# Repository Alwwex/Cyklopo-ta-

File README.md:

# CykloComp – chytrý cyklopočítač (ESP32-C3) + aplikace + PCB + krabička

Vlastní „Garmin“ na řídítka: **Waveshare ESP32-C3-Zero**, barevný displej
ST7789, GPS a Li-Po baterie. Zobrazuje rychlost, trasu s mapou ulic, tep a
kadenci z BLE senzorů, ukládá jízdy a přes Bluetooth si povídá s aplikací
v telefonu. Vzhled je inspirovaný „DS / Game Boy“ cyklopočítači – barevný
budík rychlosti a retro zelené LCD téma.

| Plošný spoj CykloPCB v1 | 3D krabička s Garmin úchytem |
|---|---|
|  |  |

## Co je v repozitáři

| Složka | Co to je |
|---|---|
| [`firmware/CykloComp/`](firmware/CykloComp/CykloComp.ino) | firmware v2 pro ESP32-C3 (Arduino IDE) |
| [`firmware/host_preview/`](firmware/host_preview/) | náhled displeje na PC – stejný kód vykreslí obrazovky do PNG (bez hardwaru) |
| [`webapp/`](webapp/README.md) | **mobilní aplikace** (PWA, Web Bluetooth) – doporučená |
| [`app/`](app/README.md) | původní React Native aplikace (kompatibilní, dál se nevyvíjí) |
| [`hardware/pcb/`](hardware/pcb/README.md) | plošný spoj ve 2 variantách: osazení u JLCPCB, nebo holá deska na ruční pájení |
| [`hardware/enclosure/`](hardware/enclosure/README.md) | 3D tištěná krabička (OpenSCAD + STL), Garmin quarter-turn |
| [`tools/usb_console.py`](tools/usb_console.py) | ladění přes USB bez telefonu |
| [`docs/NAKUP.md`](docs/NAKUP.md) | **co doobjednat** |
| [`docs/DOPORUCENI.md`](docs/DOPORUCENI.md) | web vs. nativní appka, lepší displej, lepší nabíjení |

## Rychlý start

1. **Firmware** – Arduino IDE, deska *ESP32C3 Dev Module*,
   *USB CDC On Boot: Enabled*, *Partition Scheme: Default 4MB with spiffs*.
   Knihovny: `Adafruit GFX`, `Adafruit ST7735 and ST7789`, `TinyGPSPlus`,
   `NimBLE-Arduino` **2.x**. V `CykloComp.ino` vyber `BOARD_PROFILE`
   (`BOARD_BREADBOARD` = současné zapojení, `BOARD_CYKLOPCB_V1` = nový plošný spoj)
   a nahraj. Bez GPS signálu to vyzkoušíš příkazem `SIM:1` (USB nebo appka).
2. **Aplikace** – otevři `webapp/` v Chrome na Androidu (návod na nasazení v
   [webapp/README.md](webapp/README.md)) → *Připojit CykloComp*. Bez hardwaru:
   *Vyzkoušet demo*.
3. **PCB** – buď JLC osadí malé součástky (`hardware/pcb/build/` – gerber zip
   + BOM + CPL), nebo objednáš **jen holou desku a všechno připájíš sám**
   (`hardware/pcb/build_rucni/`, velké součástky + tvůj modul TP4056)
   ([postup pro obě varianty](hardware/pcb/README.md)).
4. **Krabička** – změř displej a baterii, uprav parametry a vytiskni
   ([postup](hardware/enclosure/README.md)). Nejdřív `garmin_test.stl`!

## Firmware v2

### Ovládání

| Tlačítko | Krátce | Dlouze |
|---|---|---|
| **MODE** (BTN1) | další obrazovka | vypnout (spánek, probudí MODE – jen na PCB) |
| **START** (BTN2) | start / stop jízdy (po stopu souhrn jízdy) | vynulovat trip |
| **PAUZA** (BTN3) | při jízdě pauza/pokračovat, jinak předchozí obrazovka | přepnout téma NOC → RETRO → DEN |

První stisk při ztlumeném displeji jen rozsvítí.

### Obrazovky
1. **DASH** – barevný oblouk rychlosti (šipky = průměr a maximum), velké
   7-segmentové číslice, čas jízdy a 4 nastavitelné dlaždice (z 14 hodnot:
   trip, čas, průměr, max, výška, odometr, satelity, hodiny, stoupání, sklon,
   tep, kadence, baterie, do cíle).
2. **STATISTIKY** – kompletní přehled jízdy + odometr.
3. **MAPA** – trasa z appky, ulice z OpenStreetMap, projetá stopa, šipka směru,
   „DO CÍLE“ a rychloměrný proužek jako na Game Boyi.
4. **SYSTÉM** – GPS, poloha, HDOP, baterie, Bluetooth, senzory, verze.

### Co umí navíc proti v1
- 3 témata (**NOC** – tmavá DS deska, **RETRO** – Game Boy zelená, **DEN** – kontrast na slunce)
- **jízdy se ukládají do flash** (LittleFS, posledních 40) a appka si je stáhne → telefon nemusí být během jízdy připojený
- **autopauza**, **stoupání** (s hysterezí), **sklon**, filtrace skoků GPS a špatného HDOP
- **baterie** (%, nabíjení přes USB, varování, vypnutí při vybití), **jas podsvícení**, ztlumení při stání
- **spánek** a automatické vypnutí po nečinnosti (PCB), vypínání GPS
- **BLE senzory**: hrudní pás (Heart Rate 0x180D) a kadence (CSC 0x1816) – běží ve vlastním vlákně
- hodiny z telefonu, když GPS ještě nemá čas
- příkazy z BLE se zpracovávají ve smyčce (žádné souběhy s kreslením)
- **simulace jízdy** `SIM:1` – jede po nahrané trase, ukáže i autopauzu

Kód je jeden `.ino` (podmínka Arduino IDE – ve složce sketche jen jeden `.ino`).

### Náhled displeje na PC
`firmware/host_preview/build_preview.sh` přeloží **ten samý** `CykloComp.ino`
pro PC (displej = pole pixelů), odsimuluje jízdu a uloží PNG všech obrazovek ve
všech tématech – hodí se při úpravách vzhledu bez nahrávání do ESP.

## BLE protokol (firmware ↔ appka)

Service `a5c40001-2f0b-4f6e-9d3a-8c1e2b7d9f10`, charakteristiky `a5c4000X-…`:

| UUID | Typ | Obsah |
|---|---|---|
| `…0002` telemetrie | READ + NOTIFY, 1×/s | `{"fix","spd","lat","lng","alt","dst","tim","sat","rid","pau","bat","asc","max","hr","cad"}` (≤ 173 B) |
| `…0003` příkazy | WRITE + WRITE_NR | textové příkazy níže (≤ 255 B) |
| `…0004` stav | READ + NOTIFY, 1×/5 s | `{"fw","brd","odo","vb","chg","thm","bl","ap","sen","hrc","csc","grd","avg","hdp","crs","scr","tz","aoff","gmax","sim","apa","fs","rcur","f":[…]}` |
| `…0005` bulk | READ | odpovědi na `SYNC:*` (`{"req":"…",…}`, ≤ 512 B) |

`bat` = 0–100 %, 101 = napájení z USB, −1 = neměří se.

Příkazy:
- jízda: `RIDE:START|STOP|PAUSE|RESUME`, `RESET_TRIP`
- čas: `SET_TZ:<h>`, `TIME:<unix>`
- displej: `SCREEN:<0-3>`, `THEME:<0-2>`, `BL:<5-100>`, `GAUGE:<km/h>`, `CFG:FIELDS:a,b,c,d` (0–13)
- chování: `AP:0|1` (autopauza), `SENS:0|1` (BLE senzory), `AUTOOFF:<min>`, `ODO:<km>`, `SIM:0|1`, `PWROFF`, `INFO`
- trasa: `RT:BEGIN` / `RT:P:lat,lng;…` / `RT:END` / `RT:CLEAR`
- ulice: `MP:BEGIN` / `MP:P:…` / `MP:END` (segmenty oddělené `999,999`)
- uložené jízdy: `SYNC:LIST`, `SYNC:SUM:<id>`, `SYNC:TRK:<id>:<strana>` (24 bodů/strana), `SYNC:DEL:<id>` →
  odpověď se přečte z bulk charakteristiky (appka čte, dokud `req` neodpovídá dotazu)

Stará React Native appka funguje dál – nová pole ignoruje.

## Testování přes USB (bez telefonu)

Firmware zvládá **stejný textový protokol i po USB** (nativní USB-CDC).

1. Arduino IDE: **Tools → USB CDC On Boot → Enabled**.
2. Serial Monitor (115200) nebo `python3 tools/usb_console.py [PORT]` (`pip install pyserial`).
3. Piš příkazy (`SIM:1`, `RIDE:START`, `THEME:1`, `SYNC:LIST`…) a sleduj
   telemetrii (1×/s), `STATUS:` (1×/5 s) a odpovědi `BULK:`.
   `usb_console.py` umí `testroute` – pošle ukázkovou trasu.

## Akceptační test (ruční, na reálném HW)

1. **Připojení** – appka najde `CykloComp`, telemetrie teče do 2 s, hodiny na displeji se nastaví z telefonu.
2. **Start z appky** – oba ukazují 0:00, na displeji červená tečka.
3. **Pauza** – z appky → na ESP žluté `‖`, čas stojí; PAUZA na ESP → v appce zmizí badge.
4. **Autopauza** – při zastavení se čas po 3 s zastaví („AUTOPAUZA“).
5. **Start/stop z ESP** a **jízda bez telefonu** – po STOP souhrn jízdy; po připojení appky se jízda stáhne do Historie (s mapou a body).
6. **Trasa** – naplánovat v Mapě (nebo GPX) → *Odeslat* → na displeji trasa + ulice + „DO CÍLE“.
7. **Rychlost při stání** – `0.0`, ne GPS šum.
8. **Nastavení** – téma, jas, dlaždice 2×2 přežijí restart ESP (NVS).
9. **Baterie (PCB)** – % odpovídá napětí; s USB „USB“ + blesk; pod 10 % varování.
10. **Spánek (PCB)** – dlouhý MODE → „VYPÍNÁM“ → MODE probudí.

## Hranice systému

- Rastrové mapové dlaždice na ESP32-C3 **nejdou** (4 MB flash, 400 KB RAM) –
  firmware kreslí vektorové ulice/trasu/stopu. Upgrade cesta: ESP32-S3 + PSRAM + SD.
- Overpass / BRouter / OSRM / dlaždice OSM jsou veřejné služby – appka je
  nezatěžuje zbytečně (debounce, cache), ale výpadek na jejich straně se může stát.
- Web Bluetooth: Android Chrome ano, iPhone jen přes prohlížeč Bluefy.
- Rozměry Garmin úchytu nejsou oficiálně zveřejněné → nejdřív testovací výtisk.

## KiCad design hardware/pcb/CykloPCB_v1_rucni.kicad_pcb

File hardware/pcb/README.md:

# CykloPCB v1 – plošný spoj pro CykloComp

Nosná deska 43 × 64 mm, na kterou se připájí **Waveshare ESP32-C3-Zero**,
připojí **displej**, **GPS** a **Li-Po baterie**. Řeší všechno, co na
nepájivém poli chybělo: nabíjení přes USB-C s „power-path“, vypínač,
3,3 V stabilizátor, měření baterie, vypínání GPS a podsvícení (pro spánek)
a tři boční tlačítka.

| Horní strana | Spodní strana |
|---|---|
|  |  |

Schéma: [`schema_zapojeni.svg`](schema_zapojeni.svg) ([PNG](schema_zapojeni.png))

**Dvě varianty – vyber si:**

| | **CykloPCB v1** (JLC osadí) | **CykloPCB v1 R** (všechno pájíš sám) |
|---|---|---|
| Objednáš | desku + osazení SMD u JLCPCB | jen holou desku (~100–250 Kč za 5 ks vč. dopravy) |
| Součástky | 0603, USB-C a TP4056 přímo na desce | velké **1206**, SOT-223, SMA + **tvůj modul TP4056 USB-C** |
| Pájení | jen THT (tlačítka, konektory, ESP) | všechno, ale nic malinkého – zvládne začátečník |
| Soubory | `build/` | `build_rucni/` → [návod níž](#varianta-pro-ruční-pájení--cyklopcb-v1-r) |

Firmware je pro obě stejný (`BOARD_PROFILE BOARD_CYKLOPCB_V1`), krabička má
přepínač `pcb_variant`.

## Co je na desce

| Blok | Součástky | Proč |
|---|---|---|
| Nabíjení | USB-C (J1) + **TP4056** (U1), 600 mA, LED červená = nabíjí, zelená = nabito | stejný čip jako tvůj modul, ale… |
| **Load-sharing (power-path)** | Schottky D3 + P-MOSFET Q1 | …když je zapojené USB, CykloComp jede z USB a baterie se jen nabíjí. Modul TP4056 tohle neumí → při nabíjení za jízdy (powerbanka) baterii trvale „dobíjí“ a nikdy neukončí nabíjení. |
| Vypínač | posuvný SW1 na boku | skutečně odpojí elektroniku (0 µA), nabíjení funguje i vypnuté |
| 3,3 V | **AP2112K-3.3** (U2), 600 mA, malý úbytek | baterie se využije až do ~3,4 V |
| Měření baterie | dělič 100k/100k → GPIO0 | % baterie na displeji i v appce, poznání USB nabíjení, vypnutí při vybití |
| Spínání GPS | P-MOSFET Q2 ← GPIO10 | GPS (~25 mA) se ve spánku úplně vypne |
| Podsvícení | P-MOSFET Q3 ← GPIO7 (PWM) | jas displeje + vypnutí ve spánku (displeje s pinem BLK) |
| Tlačítka | 3× úhlové tlačítko na hraně (MODE/START/PAUZA) + J5 pro externí vodotěsná | MODE umí probudit ESP z deep sleep (GPIO5) |

Zapojení ESP32-C3-Zero (pady číslované od USB):

| Pin modulu | Funkce | Pin modulu | Funkce |
|---|---|---|---|
| 5V | **nezapojeno** (USB modulu jen na programování) | GP21 | → RX GPS |
| GND | GND | GP20 | ← TX GPS |
| 3V3 | 3,3 V z desky | GP19, GP18 | – |
| GP0 | měření baterie | GP10 | zapnutí GPS |
| GP1–GP4 | TFT RST, DC, CS, SCLK | GP9 | tlačítko PAUZA (= BOOT) |
| GP5 | tlačítko MODE (probouzí) | GP8 | tlačítko START |
| | | GP7 / GP6 | podsvícení PWM / TFT MOSI |

> ⚠️ **Před objednáním zkontroluj** rozložení pinů svého modulu ESP32-C3-Zero
> proti potisku na desce (u každé plošky je napsané GPIO). Vychází z
> dokumentace Waveshare (pady 1–3 = 5V/GND/3V3, pady 4–14 = GP0–GP10). Řady pinů
> jsou na footprintu 17,78 mm od sebe a plošky jsou prodloužené, takže modul jde
> připájet přes kolíkovou lištu i naplocho za půlotvory na okraji.

## Jak objednat u JLCPCB (orientačně 30–60 € za 5 desek, z toho 2 osazené, vč. dopravy a DPH)

1. Na <https://jlcpcb.com> → **Order now** → **Add gerber file** →
   nahraj `build/CykloPCB_v1_gerber_JLCPCB.zip`.
2. Parametry nech výchozí: 2 vrstvy, 1,6 mm, HASL (lead free je hezčí),
   barva libovolná (zelená je nejlevnější a nejrychlejší), 5 ks.
3. Zapni **PCB Assembly** → *Economic*, **Top side**, počet osazených 2 nebo 5.
4. Nahraj **BOM** `build/CykloPCB_v1_BOM_JLCPCB.csv` a **CPL**
   `build/CykloPCB_v1_CPL_JLCPCB.csv`.
5. V náhledu osazení **zkontroluj otočení** součástek (hlavně TP4056 – tečka =
   pin 1, MOSFETy, LED a USB-C). Když něco sedí natočené, JLC ho otočí
   tlačítkem *Rotate* přímo v náhledu. Typicky bývá potřeba otočit USB-C a SOT-23.
6. Pokud některá součástka není skladem, JLC nabídne náhradu (rezistory /
   kondenzátory klidně, u TP4056/AP2112K vyber stejný čip jiného výrobce).

JLC osadí jen SMD součástky nahoře. **Ručně připájíš** (seznam
`build/CykloPCB_v1_rucni_osazeni.csv`):

| Pozice | Díl | Kde koupit |
|---|---|---|
| U3 | Waveshare ESP32-C3-Zero (máš) | – |
| SW1 | posuvný přepínač C&K OS102011MA1QN1 (úhlový, 2,54 mm) | TME, Mouser, AliExpress „OS102011MA1Q“ |
| SW2–SW4 | úhlové tlačítko 6×6 mm C&K PTS645VL31-2 LFS (nebo kompatibilní) | TME, Mouser |
| J4 | JST PH 2,0 mm 2pin horizontální (S2B-PH-K) | TME, AliExpress |
| J2, J3, J5 | kolíková lišta 2,54 mm (nebo rovnou připájet vodiče) | kdekoli |

## Postup oživení (důležité – v tomhle pořadí)

1. **Bez baterie a bez ESP**: připoj USB-C (NABÍJENÍ). Červená LED musí
   blikat/svítit (nabíječka bez baterie). Multimetrem: VSW ≈ 4,6 V (vypínač ON),
   3V3 = 3,3 V. Teprve pak dál.
2. **Zkontroluj polaritu baterie!** Čínské Li-Po s konektorem JST PH mívají
   prohozené kabely. Na desce je u J4 potisk **+** a **−**. Případně kabely
   v konektoru přehoď (jehlou nadzvedni západku).
3. Baterie **musí mít ochranný obvod (PCM)** – u 103450 bývá pod páskou na
   vývodech malá destička. Deska ochranu proti podvybití nemá (hlídá ji firmware
   + PCM v baterii).
4. Připájej ESP32-C3-Zero, tlačítka, vypínač, konektory.
5. Ve firmwaru nastav `#define BOARD_PROFILE BOARD_CYKLOPCB_V1`
   (v `firmware/CykloComp/CykloComp.ino`) a nahraj přes USB-C **na modulu ESP**.

## Varianta pro ruční pájení – CykloPCB v1 R

| Deska | Osazovací výkres (hodnoty součástek) |
|---|---|
|  |  |

Stejná velikost, displej, GPS, boční tlačítka a piny ESP jako v1 – místo USB-C
a nabíječky na desce se **nalepí tvůj modul TP4056 USB-C** a ostatní součástky
jsou velké (1206 = 3,2 × 1,6 mm, rozšířené plošky „HandSolder“).

Rozdíly proti v1 (a proti [schématu](schema_zapojeni.svg), které kreslí v1):

- **A1 = modul TP4056** místo J1, U1, R1–R5, C1, C2, D1, D2 (USB-C, nabíječka, LED).
- **J4 pin 2 = B-** (vede do modulu na jeho B-), ne GND. **JP1** = pájecí můstek B- ↔ GND.
- **U2 = MCP1825S-3302E/DB** v SOT-223 (1 VIN, 2 + chladicí ploška GND, 3 VOUT;
  500 mA, klidový proud ~120 µA) místo AP2112K.
- Jen **3 montážní díry** (H3 v rohu pod modulem odpadá), vypínač SW1, J4 a J5
  jsou jinde → krabička s `pcb_variant = "rucni"`.
- GND plošky SMD součástek mají tepelné můstky (jdou snadno zapájet).

**Objednání:** na JLCPCB nahraj jen `build_rucni/CykloPCB_v1_rucni_gerber_JLCPCB.zip`,
5 ks, 2 vrstvy, 1,6 mm, HASL lead free, **PCB Assembly vypnuté**.
Součástky: [`build_rucni/CykloPCB_v1_rucni_soucastky.csv`](build_rucni/CykloPCB_v1_rucni_soucastky.csv)
(hodnota, kusy, označení na desce, kde koupit) a [nákupní seznam](../../docs/NAKUP.md).

### Nabíjecí modul TP4056 USB-C (ten, co už máš)

- Max. **19 × 30 mm** včetně přesahu USB-C (běžné moduly mají 25–28,4 × 17–17,8 mm).
  Před objednáním desky ho změř.
- Nalep ho **oboustrannou pěnovou páskou ~1 mm** do čárkovaného obdélníku,
  USB-C k dolní hraně desky. Strana „+“ modulu (IN+, B+, OUT+) je při pohledu
  shora s USB-C dole **vlevo** (je to i na potisku).
- 4 drátky (silikonový 26 AWG, cca 5–30 mm) z plošek modulu na řadu plošek nad ním:

| Plošky na modulu | → plošky na desce | Síť |
|---|---|---|
| IN+ (u USB-C, vlevo) | **IN+** (drátek podél levé strany modulu) | VBUS – detekce USB + load sharing |
| OUT+ (nebo B+, je to totéž) | **OUT+** | BAT+ |
| B- | **B-** | minus baterie (z J4) |
| OUT- | **OUT-** | GND |
| IN- | nic | – |

> ⚠️ **B- nikdy nespojuj s GND** – obešla by se ochrana modulu (DW01 + 8205).
> Baterie se zapojí do **J4** (potisk **+** a **B-**), deska ji pošle do modulu.
>
> Máš modul **bez ochrany** (jen 4 plošky IN+ IN- B+ B-)? IN+ → IN+, B+ → OUT+,
> B- → OUT- a **zakápni cínem pájecí můstek JP1** (B- = GND). Ochranu pak dělá
> jen PCM v baterii.

- Nabíjí ~1 A (Rprog 1,2 kΩ) → použij nabíječku aspoň **1,5–2 A**, ne USB v PC.
  Při 1 A čip hřeje až ~1,3 W a v krabičce leží **pod baterií** → doporučuju na
  modulu vyměnit Rprog (~1,2 kΩ u vývodu 2 TP4056) za **2,4 kΩ** → ~500 mA
  (jako JLC verze). Plné nabití pak trvá ~4–5 h.
- Hodně levných modulů **nemá na USB-C odpory 5,1 kΩ (CC)** – pak nenabíjí
  z nabíječky USB-C → USB-C, jen kabelem **USB-A → USB-C**. Vyzkoušej předem.
- LED modulu prosvítí okénkem v levé stěně krabičky (`pcb_variant = "rucni"`).
- Čelo USB-C modulu má být **zarovnané s hranou desky** (nebo 1–2 mm přes ni,
  do otvoru v krabičce) a vnitřní konec modulu přichyť kapkou tavného lepidla
  nebo epoxidu – samotná páska při zasouvání kabelu povolí.

### Pořadí pájení

Nástroje: mikropájka s teplotou (Pinecil / TS101 / stanice), hrot sekáček
1,6–2,4 mm, cín 0,5–0,7 mm, **tavidlo**, knot, pinzeta, multimetr, lupa nebo foťák telefonu.

1. **Rezistory a kondenzátory 1206** (podle osazovacího výkresu): pocínuj jednu
   plošku, pinzetou přilož součástku, prohřej, pak druhou stranu.
2. **MOSFETy Q1–Q3 (SOT-23)** – stejný postup, jeden vývod je sám na jedné straně.
3. **LDO U2 (SOT-223)** – nejdřív vývod 1, pak 2 a 3, nakonec velkou chladicí
   plošku (GND, potřebuje víc tepla ~350–380 °C a tavidlo).
4. **Dioda D3 (SMA)** – proužek (katoda) k ploše **vlevo, u písmene K** (k vypínači).
5. THT: vypínač SW1, tlačítka SW2–4 (zatlač až k desce, ať sedí s krabičkou),
   J4, lišty J2, J3 (J5 jen pro externí tlačítka).
6. Modul TP4056: drátky nejdřív na modul, pak přilepit, pak na desku.
7. ESP32-C3-Zero úplně nakonec (**USB-C ESP dolů** k hraně, je to na potisku).

**Kontrola před zapnutím** (bez baterie), multimetrem na pípání – nic z toho nesmí pípat:
3V3–GND, VSW–GND, **J4 + ↔ J4 B-** (zkrat baterie) a u modulu s ochranou
**B- ↔ GND** (JP1 musí zůstat rozpojený).

Pak USB do modulu, vypínač ON: VSW ≈ 4,4–4,7 V, 3V3 = 3,3 V. Potom baterie
(**polarita!**) a znovu 3V3 bez USB. Když po připojení baterie nic nejde, připoj
na chvíli USB do modulu – tím se „probudí“ jeho ochrana (DW01). Teprve pak ESP.

> Vypínač OS102011MA1QN1 je katalogově na 100 mA a vede celý odběr (~0,1–0,3 A při
> 4 V). V hobby zapojeních to běžně funguje; když chceš rezervu, kup posuvný
> přepínač se stejnou roztečí vývodů a proudem ≥ 0,5 A.

Generování: `python3 generate_pcb.py --variant hand --freerouting /cesta/k/freerouting-1.9.0.jar`
a `python3 render_preview.py hand`.

## Jak deska vznikla / úpravy

Deska se generuje skriptem – nic se nekreslí ručně:

```bash
cd hardware/pcb
python3 generate_pcb.py --freerouting /cesta/k/freerouting-1.9.0.jar
python3 render_preview.py      # náhledy PNG
python3 schematic.py           # schéma
```

- `generate_pcb.py` – seznam součástek, spojů a pozic → KiCad deska →
  autorouter **Freerouting** → rozlití země → **DRC** → Gerber/vrtání/BOM/CPL/STEP.
- `CykloPCB_v1.kicad_pcb` – otevřeš v **KiCadu 7+** a můžeš cokoliv upravit ručně
  (pak exportuj Gerbery z KiCadu: *File → Fabrication Outputs*).
- `build/drc.rpt` – kontrola návrhových pravidel: 0 porušení, 0 nepřipojených
  plošek (řádky `lib_footprint_issues` = jen chybějící tabulka knihoven, nevadí). Když deska není čistá, skript výrobní data **nevytvoří** (`--force` to obejde).
- `build/CykloPCB_v1.step` – 3D model desky (pro kontrolu v krabičce).

Pravidla jsou nastavená bezpečně pro JLCPCB: cesty ≥ 0,25 mm (napájení 0,5 mm),
mezery ≥ 0,2 mm, prokovy 0,7/0,3 mm (mezikruží 0,2 mm), měď ≥ 0,45 mm od rovných
hran (v zaoblených rozích a u pinu 1 modulu ESP ≥ 0,3 mm).

### JLCPCB DFM kontrola (po úpravách v2)

| Kontrola | Co se změnilo |
|---|---|
| Slot width (4 chyby) | sloty stínění USB-C 0,6 → **0,7 mm** (plošky 1,1 mm) |
| Annular ring (62 varování) | prokovy 0,6/0,3 → **0,7/0,3 mm** |
| tht to smd (1 chyba + 6 varování) | zemnicí prokovy už nejsou **v** plošce TP4056 (EP), ale 0,3 mm vedle, napojené cestou 0,5 mm; autorouter drží prokovy ≥ 0,3 mm od SMD plošek; LED + rezistory posunuté dál od pinů modulu ESP32-C3-Zero |
| Silkscreen to hole (4 chyby) | potisk se po routování ořízne ≥ 0,25 mm od každého otvoru a ≥ 0,2 mm od hrany desky, značky pinu 1 a texty se odsunou |
| Silkscreen line width (50) | všechen potisk ≥ **0,16 mm** |
| Negative soldermask expansion (38) | maska +0,05 mm kolem plošek (USB-C +0,025 mm) |
| Soldermask multiple segments (4) | zdvojené plošky USB-C (A1/B12…) už nemají dvojitý otvor v masce |
| Pad spacing (1 varování) | **bez změny** – rozteč 0,5 mm konektoru USB-C (mezera 0,2 mm), JLC vyrábí od 0,15 mm, s osazením JLC to je běžné |

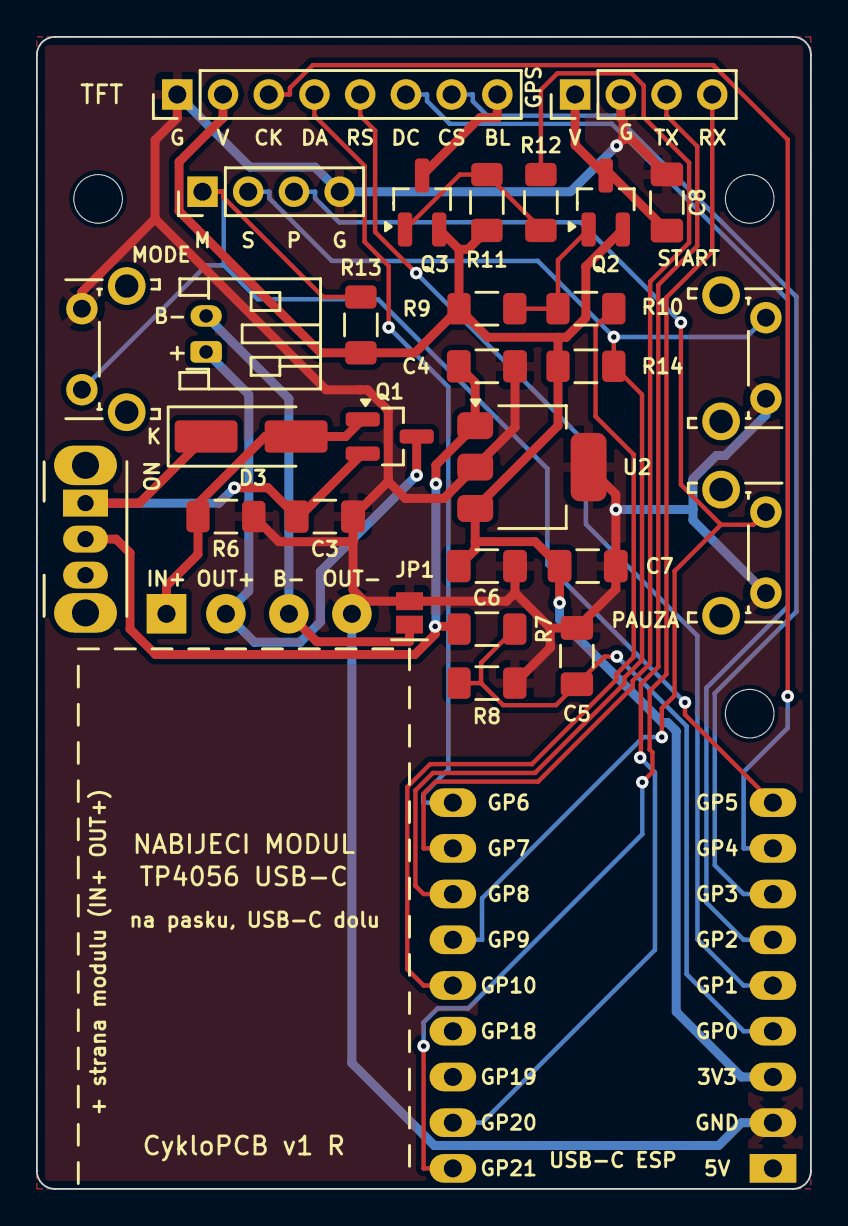
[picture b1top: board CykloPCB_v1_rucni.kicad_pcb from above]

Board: 2 copper layers, 43.0 x 64.0 mm, 34 parts (0 on the bottom side), 24 nets.

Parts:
A1: TP4056 USB-C modul; TP4056_TypeC_module_wired
C3, C4, C6: 10uF; C_1206_3216Metric_Pad1.33x1.80mm_HandSolder
C5, C7, C8: 100nF; C_1206_3216Metric_Pad1.33x1.80mm_HandSolder
D3: SS34; D_SMA_Handsoldering
H1, H2, H4: M2.5; MountingHole_2.7mm_M2.5
J2: TFT; PinHeader_1x08_P2.54mm_Vertical
J3: GPS; PinHeader_1x04_P2.54mm_Vertical
J4: LiPo 3.7V; JST_PH_S2B-PH-K_1x02_P2.00mm_Horizontal
J5: BTN ext; PinHeader_1x04_P2.54mm_Vertical
JP1: B- = GND; SolderJumper-2_P1.3mm_Open_Pad1.0x1.5mm
Q1, Q2, Q3: AO3401A; SOT-23_Handsoldering
R6, R7, R8, R9, R11, R13: 100k; R_1206_3216Metric_Pad1.30x1.75mm_HandSolder
R10, R12: 1k; R_1206_3216Metric_Pad1.30x1.75mm_HandSolder
R14: 10k; R_1206_3216Metric_Pad1.30x1.75mm_HandSolder
SW1: ON/OFF; SW_Slide_SPDT_Angled_CK_OS102011MA1Q
SW2: MODE; SW_Tactile_SPST_Angled_PTS645Vx31-2LFS
SW3: START; SW_Tactile_SPST_Angled_PTS645Vx31-2LFS
SW4: PAUSE; SW_Tactile_SPST_Angled_PTS645Vx31-2LFS
U2: MCP1825S-3302E/DB; SOT-223-3_TabPin2
U3: ESP32-C3-Zero

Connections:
3V3: C6.1, C7.1, J2.2, Q2.2, Q3.2, R9.1, R11.1, R13.1, R14.1, U2.3, U3.3
BAT+: A1.2, J4.1, Q1.3
BAT_SENSE: C5.1, R7.2, R8.1, U3.4
BL_G: Q3.1, R11.2, R12.1
BL_PWM: R12.2, U3.11
BNEG: A1.3, J4.2, JP1.1
BTN1: J5.1, R13.2, SW2.1, U3.9
BTN2: J5.2, R14.2, SW3.1, U3.12
BTN3: J5.3, SW4.1, U3.13
GND: A1.4, C3.2, C4.2, C5.2, C6.2, C7.2, C8.2, J2.1, J3.2, J5.4, JP1.2, R6.2, R8.2, SW2.2, SW3.2, SW4.2, U2.2, U3.2
GPS_EN: R10.2, U3.14
GPS_G: Q2.1, R9.2, R10.1
GPS_RXD: J3.4, U3.18
GPS_TXD: J3.3, U3.17
GPS_VCC: C8.1, J3.1, Q2.3
SYS: C3.1, D3.1, Q1.2, SW1.1
TFT_BLK: J2.8, Q3.3
TFT_CS: J2.7, U3.7
TFT_DC: J2.6, U3.6
TFT_MOSI: J2.4, U3.10
TFT_RST: J2.5, U3.5
TFT_SCLK: J2.3, U3.8
VBUS: A1.1, D3.2, Q1.1, R6.1
VSW: C4.1, R7.1, SW1.2, U2.1

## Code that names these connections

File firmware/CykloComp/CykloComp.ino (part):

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
#if BOARD_PROFILE == BOARD_CYKLOPCB_V1
  #define BOARD_NAME        "CykloPCB v1"
  #define BTN1_PIN          5    // MODE / zapnout (umi probudit z deep sleep)
  #define BTN2_PIN          8    // START / STOP
  #define BTN3_PIN          9    // PAUZA / ZPET (zaroven BOOT tlacitko)
  #define BAT_ADC_PIN       0    // delic 100k/100k z napajeci vetve
  #define TFT_BL_PIN        7    // P-MOSFET, aktivni v LOW
  #define TFT_BL_ACTIVE_LOW 1
  #define GPS_EN_PIN        10   // P-MOSFET, aktivni v LOW
  #define GPS_EN_ACTIVE_LOW 1
  #define WAKE_BTN_PIN      5
#else
  #define BOARD_NAME        "Breadboard"
  #define BTN1_PIN          8
  #define BTN2_PIN          9
  #define BTN3_PIN          10
  // Mereni baterie: pridej delic 2x100k z TP4056 OUT+ na GPIO0 a dej sem 0.
  #define BAT_ADC_PIN       -1
  #define TFT_BL_PIN        -1   // displej bez BLK pinu - podsviceni stale zapnute
  #define TFT_BL_ACTIVE_LOW 0
  #define GPS_EN_PIN        -1
  #define GPS_EN_ACTIVE_LOW 0
  #define WAKE_BTN_PIN      -1   // GPIO8-10 neumi probudit C3 z deep sleep
#endif
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// ============================================================================
// PINY (spolecne)
// ============================================================================
#define TFT_CS    3
#define TFT_DC    2
#define TFT_RST   1
#define TFT_MOSI  6
#define TFT_SCLK  4

#define GPS_RX_PIN 20   // do ESP (GPS TX -> sem)
#define GPS_TX_PIN 21   // z ESP (do GPS RX)
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char serialCmdBuf[CMD_MAX_LEN];
int serialCmdLen = 0;

ButtonState btn1 = {BTN1_PIN, false, false, 0, 0, false, 2000};
ButtonState btn2 = {BTN2_PIN, false, false, 0, 0, false, 2000};
ButtonState btn3 = {BTN3_PIN, false, false, 0, 0, false, 1500};

// overlay (souhrn jizdy, hlasky)
bool overlayActive = false;
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}

void gpsPower(bool on) {
#if GPS_EN_PIN >= 0
  pinMode(GPS_EN_PIN, OUTPUT);
  digitalWrite(GPS_EN_PIN, (on ^ (GPS_EN_ACTIVE_LOW != 0)) ? HIGH : LOW);
#else
  (void)on;
#endif
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// SETUP / LOOP
// ============================================================================
void setup() {
  pinMode(BTN1_PIN, INPUT_PULLUP);
  pinMode(BTN2_PIN, INPUT_PULLUP);
  pinMode(BTN3_PIN, INPUT_PULLUP);
  gpsPower(true);

  loadPreferences();
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
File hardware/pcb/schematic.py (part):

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    d += e.Schottky().at(vb).right(2.4).label('D3 SS34', loc='top', fontsize=9)
    d += e.Dot()
    sys_n = d.here
    netlabel(d, sys_n, 'SYS', 'top')
    # Q1: BAT+ -> SYS, gate = VBUS (pri USB zavreny)
    d += e.Line().at(sys_n).down(1.0)
    q1 = e.PFet(bulk=False).right().anchor('source').label('Q1 AO3401A', loc='left', fontsize=9)
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    d += e.Switch().at(s2).right(2.0).label('SW1 ON/OFF', loc='top', fontsize=9)
    d += e.Dot()
    vsw = d.here
    netlabel(d, vsw, 'VSW', 'top')
    d += e.Capacitor().at(vsw).down(1.6).label('C4 10µ', loc='bottom', fontsize=9)
    d += e.Ground()
    d += e.Line().at(vsw).right(1.4)
    u2 = e.Ic(pins=[e.IcPin(name='VIN', pin='1', side='left'), e.IcPin(name='EN', pin='3', side='left'),
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    d += e.Ground()
    # delic pro mereni baterie
    xdv = v33[0] + 3.0
    netlabel(d, (xdv, y + 1.0), 'VSW', 'top')
    d += e.Line().at((xdv, y + 1.0)).down(0.6)
    d += e.Resistor().down(1.6).label('R7 100k', loc='bottom', fontsize=9)
    d += e.Dot()
    bs = d.here
    d += e.Line().at(bs).right(0.8)
    netlabel(d, d.here, 'BAT_SENSE → GP0')
    d += e.Resistor().at(bs).down(1.6).label('R8 100k\nC5 100n', loc='bottom', fontsize=9)
    d += e.Ground()

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        'J3 GPS (ATGM336H / NEO-6M):  1 VCC=GPS_VCC · 2 GND · 3 TX modulu → GP20 · 4 RX modulu ← GP21\n'
        'J5 externí (vodotěsná) tlačítka:  1 MODE · 2 START · 3 PAUZA · 4 GND      (paralelně k SW2–SW4)\n'
        'SW2 MODE → GP5 (R13 100k na 3V3, probouzí z deep sleep) · SW3 START → GP8 (R14 10k) · SW4 PAUZA → GP9 · všechna proti GND\n'
        'C8 100n blokuje GPS_VCC · USB-C na modulu ESP slouží jen k programování (pin 5V modulu není zapojen).',
        loc='right', fontsize=10, halign='left', valign='top')

    d.save(os.path.join(HERE, 'schema_zapojeni.svg'))
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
